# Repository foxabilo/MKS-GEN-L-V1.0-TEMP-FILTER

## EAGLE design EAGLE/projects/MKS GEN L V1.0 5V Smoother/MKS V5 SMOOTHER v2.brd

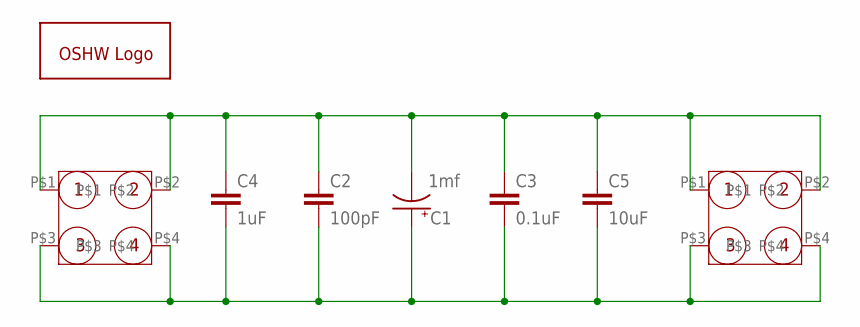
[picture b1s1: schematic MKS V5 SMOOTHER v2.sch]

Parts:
C1: 1mf; CPOL-RADIAL-5MM-10MM-KIT
C2: 100pF; 0603
C3: 0.1uF; 0603
C4: 1uF; C0805K
C5: 10uF; C0805K
GOLD_ORB_SM1: OSHWLOGOLOGO5MM; OSHW_5MM
U$1, U$2: 4BLOCK254

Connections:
unnamed: C1.-, C2.1, C3.1, C4.1, C5.1, U$1.P$1, U$1.P$2, U$2.P$1, U$2.P$2
unnamed: C1.+, C2.2, C3.2, C4.2, C5.2, U$1.P$3, U$1.P$4, U$2.P$3, U$2.P$4

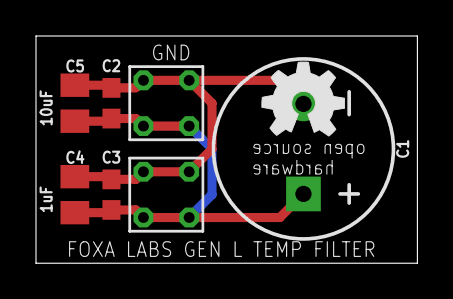
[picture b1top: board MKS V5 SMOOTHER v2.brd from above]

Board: 2 copper layers, 21.2 x 12.6 mm, 8 parts (1 on the bottom side), 2 nets.

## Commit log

2019-04-06 MKS GEN L V1.0 TEMP FILTER PCB
    MKS GEN L V1.0 has a poorly regulated and filtered 5v rail, this capacitive filter board aims to reduce the error itroduced into the ATMEGA2560 ADC lines used to messure 100K thermocouples
2019-04-06 removed temp files

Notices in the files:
parts and their libraries:
SparkFun-Capacitors: Licensing: Creative Commons ShareAlike 4.0 International - https://creativecommons.org/licenses/by-sa/4.0
